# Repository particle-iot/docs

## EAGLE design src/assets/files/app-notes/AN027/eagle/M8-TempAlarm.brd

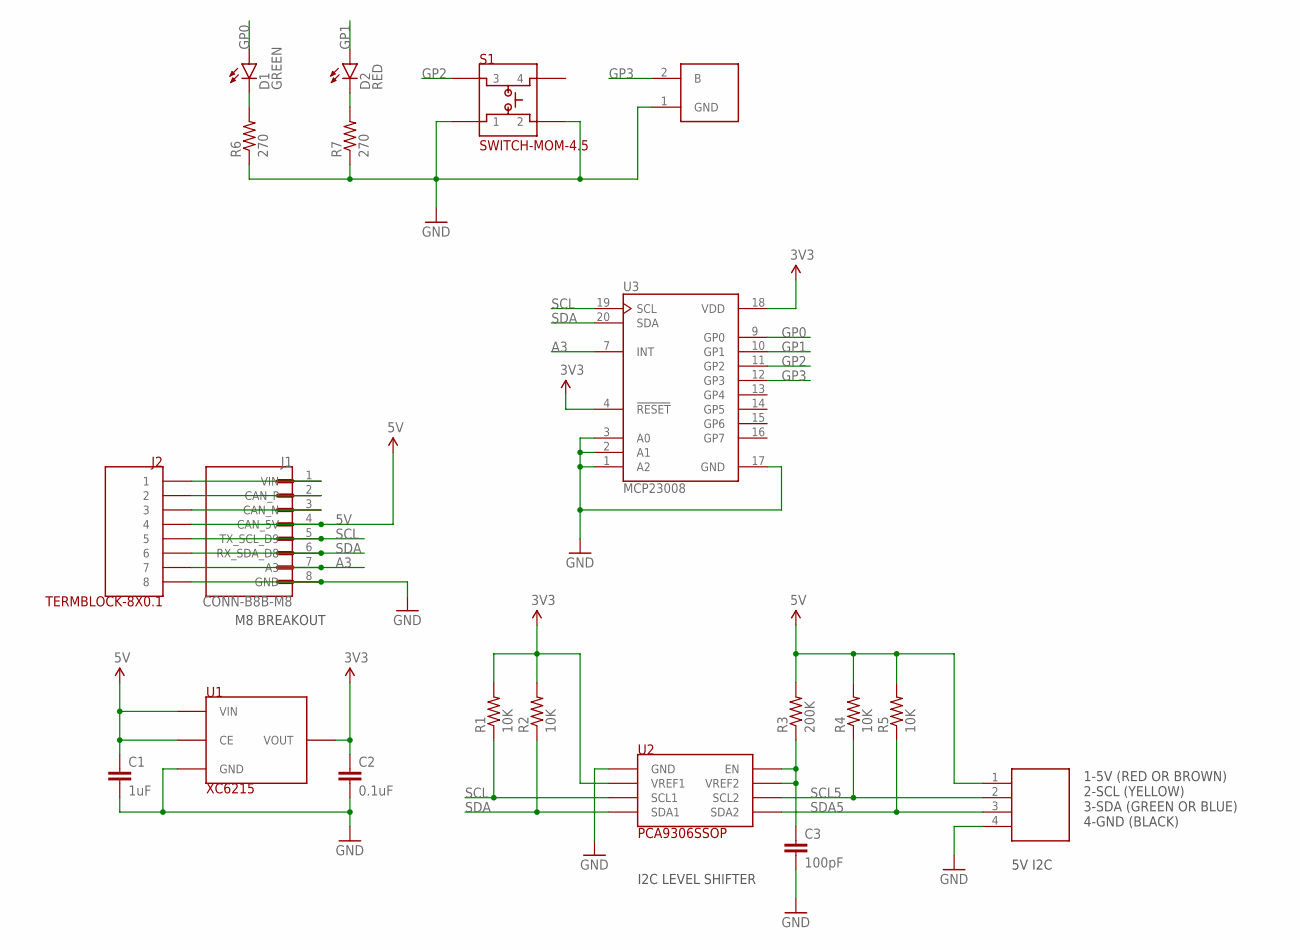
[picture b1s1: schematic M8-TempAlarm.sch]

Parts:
C1: 1uF; 0603-CAP
C2: 0.1uF; 0603-CAP
C3: 100pF; 0603-CAP
D1: GREEN; LED-0603
D2: RED; LED-0603
J1: CONN-B8B-M8; JST_B8B-PH-SM4-TB(LF)(SN)
J2: TERMBLOCK-8X0.1
R1, R2, R4, R5: 10K; 0603-RES
R3: 200K; 0603-RES
R6, R7: 270; 0603-RES
S1: SWITCH-MOM-4.5
U1: XC6215; SOT-25-TOREX
U2: PCA9306SSOP; 8-SSOP-TI
U3: MCP23008; QFN21P50_400X400X100L40X24T270N
U$1: TERMBLOCK-4X0.15
U$2: BUZZER2

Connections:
3V3: C2.1, R1.2, R2.2, U1.5 (VOUT), U2.2 (VREF1), U3.4 (!RESET), U3.18 (VDD)
5V: C1.1, J1.4 (CAN_5V), J2.P$4 (4), R3.2, R4.2, R5.2, U1.1 (VIN), U1.3 (CE), U$1.1
A3: J1.7 (A3), J2.P$7 (7), U3.7 (INT)
CAN_N: J1.3 (CAN_N), J2.P$3 (3)
CAN_P: J1.2 (CAN_P), J2.P$2 (2)
GND: C1.2, C2.2, C3.2, J1.8 (GND), J2.P$8 (8), R6.1, R7.1, S1.1, S1.2, U1.2 (GND), U2.1 (GND), U3.1 (A2), U3.2 (A1), U3.3 (A0), U3.17 (GND), U$1.4, U$2.1 (GND)
GP0: D1.A, U3.9 (GP0)
GP1: D2.A, U3.10 (GP1)
GP2: S1.3, U3.11 (GP2)
GP3: U3.12 (GP3), U$2.2 (B)
unnamed: D2.C, R7.2
unnamed: D1.C, R6.2
SCL: J1.5 (TX_SCL_D9), J2.P$5 (5), R1.1, U2.3 (SCL1), U3.19 (SCL)
SCL5: R4.1, U2.6 (SCL2), U$1.2
SDA: J1.6 (RX_SDA_D8), J2.P$6 (6), R2.1, U2.4 (SDA1), U3.20 (SDA)
SDA5: R5.1, U2.5 (SDA2), U$1.3
VIN: J1.1 (VIN), J2.P$1 (1)
VREF2_EN: C3.1, R3.1, U2.7 (VREF2), U2.8 (EN)

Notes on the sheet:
M8 BREAKOUT
I2C LEVEL SHIFTER
5V I2C
1-5V (RED OR BROWN) 2-SCL (YELLOW) 3-SDA (GREEN OR BLUE) 4-GND (BLACK)

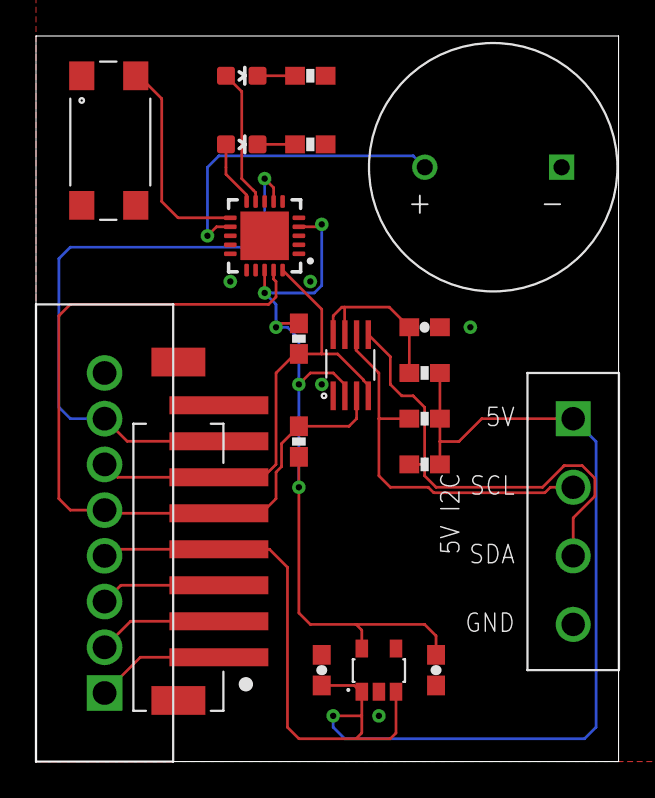
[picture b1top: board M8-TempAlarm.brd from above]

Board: 2 copper layers, 32.4 x 40.3 mm, 20 parts (0 on the bottom side), 18 nets.
